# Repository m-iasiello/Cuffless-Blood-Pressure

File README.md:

# Cuffless-Blood-Pressure
Cuffless Blood Pressure monitor using custom PCB developed from AD8232 HRM and Si1143 pulse ox.  Includes several .ino, pcb schems, and solidworks builds.

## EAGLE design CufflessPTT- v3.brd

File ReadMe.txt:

This folder contains the relevant schematic and files for the Spring 2018 Cuffless Blood Pressure Measurement Project

Contents:

	Powerpoints
		- Tutorial Presentation: Background information and initial project proposal
		- Update Presentations: Updates on progress through the semester
		- Final Presentation: Overall presentation of the project, work, and results

	Schematic and PCB Layout
		- CufflessPTT-v3.sch: The Eagle schematic for the PTT Measurement PCB 
		- CufflessPTT-v3.brd: The Eagle layout for the PTT Measurement PCB

	Software
		- PTT-BP.ino: The main Arduino code file for BP measurement.  
		- QRS_detection.ino: QRS detection algorithm for R wave detection
		- Si1143_pulse_demo.ino: Driver software for the Si1143, as well as helper functions for identification of the PPG signals
		- CUFFLESS.apk: Installer file for the Cuffless Android app.

	Solidworks Files
		- CAD files for the Cuffless case, as well as the locking pin to hold the case together.

Instructions for use:
	
	1. Install the Android app on an Android phone. 
	2. Press the button on the side to turn on the device. The LEDs should come on.
	3. Pair the Android app with the device by opening the app, and then find and pair to the device named HC-06.
	4. Press the start measurement button.
	5. Hold the electrode side of the device against the inside of your wrist. 
	6. Hold one finger of your opposite firmly on the electrdoe on top, and another finger firmly across the LEDs and photodiode.
	7. The device should display measurements as they are acquired.

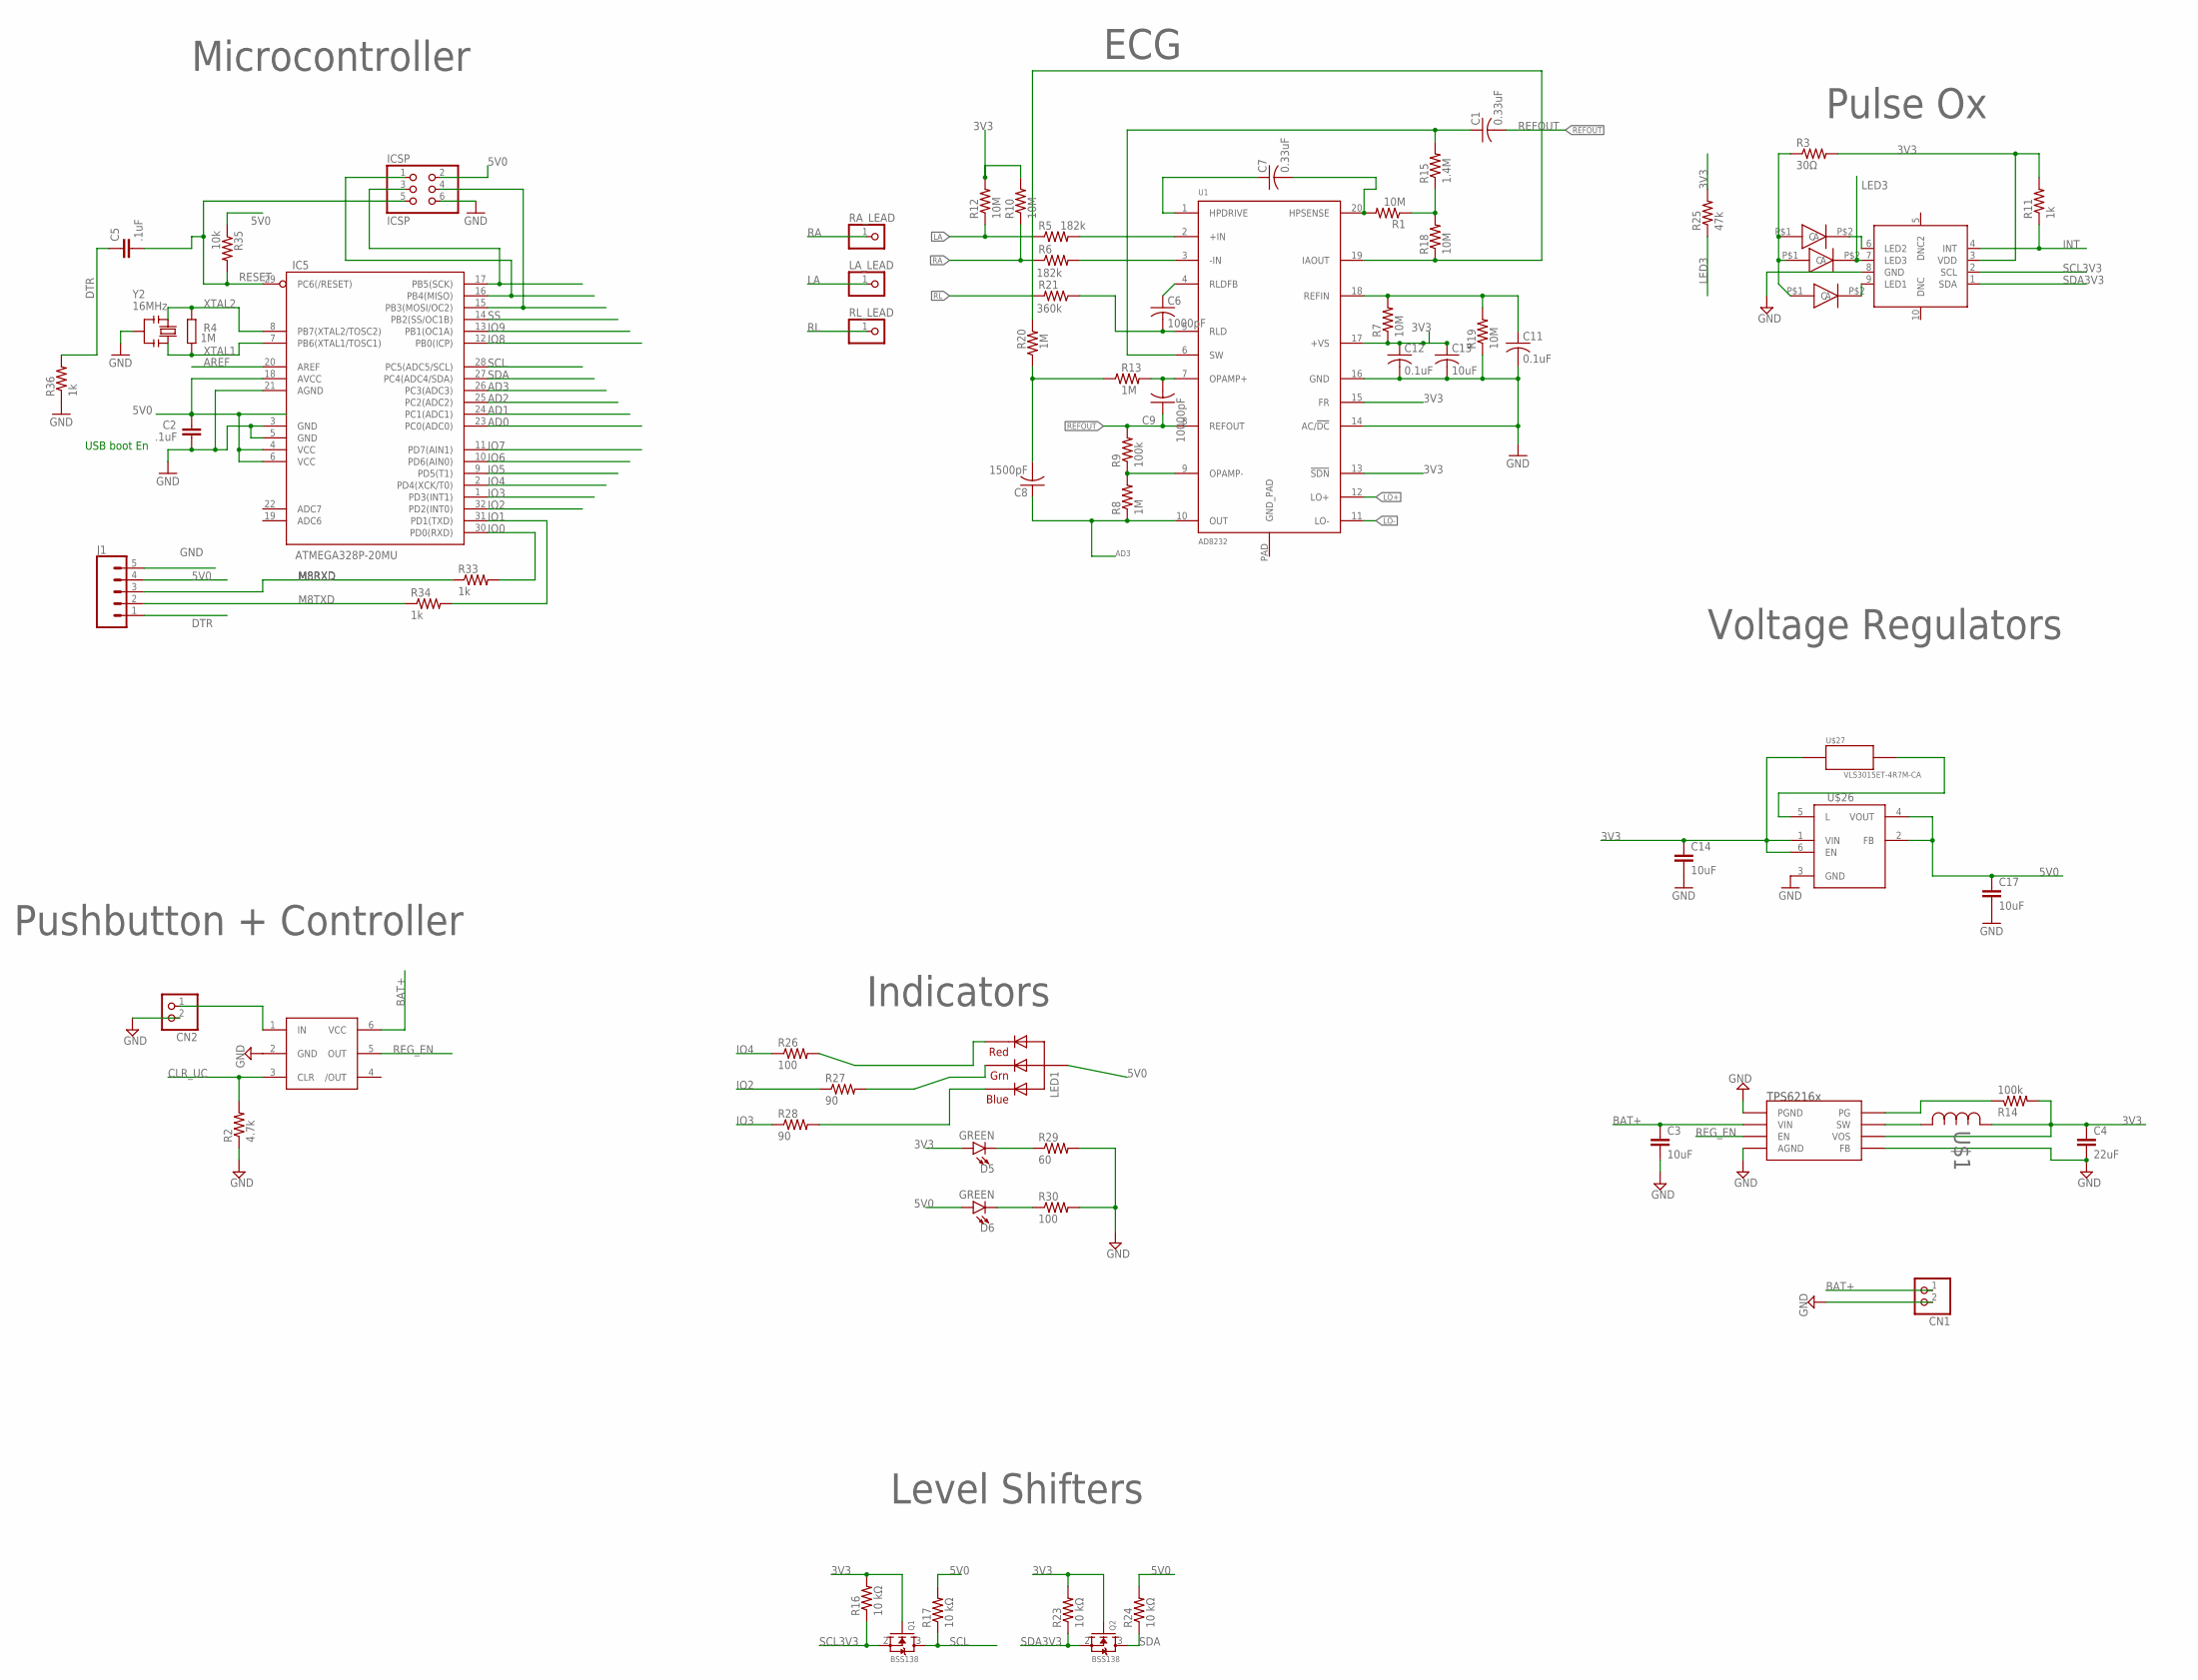
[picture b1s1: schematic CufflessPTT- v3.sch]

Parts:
C1, C7: 0.33uF; C0603
C2, C5: .1uF; C0603-ROUND
C3, C14, C17: 10uF; C0603; MPN MCNP16V105M5X11
C4: 22uF; C0805
C6: 1000pF; C0603
C8: 1500pF; C0603
C9: 10000pF; C0603
C11, C12: 0.1uF; C0603
C13: 10uF; C0603
CN1, CN2: JST_2PIN-THM; JST-PH-2-THM
D5, D6: GREEN; LED-0603
IC5: ATMEGA328P-20MU; MLF32
ICSP: ICSP; 2X03
J1: CONN_05; 1X05
LA_LEAD: PINHD-1X1; 1X01
LED1: RGBLED_CA-5MM; LED5MMRGB
LED2, LED3, LED4: SMD_COMBO
Q1, Q2: BSS138; SOT23-3
R1, R7, R10, R12, R18, R19: 10M; 0603-RES
R2: 4.7k; R0402
R3: 30Ω; R0402
R4: 1M; R0603-ROUND
R5, R6: 182k; 0603-RES
R8, R13, R20: 1M; 0603-RES
R9: 100k; 0603-RES
R11, R33, R34, R36: 1k; R0402
R14: 100k; R0402
R15: 1.4M; 0603-RES
R16, R17, R23, R24: 10 kΩ; R0402
R21: 360k; 0603-RES
R25: 47k; R0402
R26, R30: 100; R0402
R27, R28: 90; R0402
R29: 60; R0402
R35: 10k; R0402
RA_LEAD: PINHD-1X1; 1X01
RL_LEAD: PINHD-1X1; 1X01
U1: AD8232; LFCSP_20
U$1: VLF3012ST-2R2M1R4; IND_3010
U$4: SI1143; QFN-10
U$5: TPS6216X; 8WSON
U$15: MAX16054; TSOT23-6
U$26: TPS61222; SOT363_6SOIC
U$27: VLS3015ET-4R7M-CA
Y2: 16MHz; RESONATOR

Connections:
3V3: C4.1, C12.1, C13.1, C14.1, D5.A, Q1.1 (G), Q2.1 (G), R3.2, R7.1, R10.2, R11.2, R12.2, R14.2, R16.2, R23.2, R25.2, U1.13 (!SDN), U1.15 (FR), U1.17 (+VS), U$1.1, U$4.3 (VDD), U$5.P$6 (VOS), U$26.1 (VIN), U$26.6 (EN), U$27.1
5V0: C2.2, C17.1, D6.A, IC5.4 (VCC), IC5.6 (VCC), IC5.18 (AVCC), ICSP.2, J1.4, LED1.2 (VCC), R17.2, R24.2, R35.1, U$26.2 (FB), U$26.4 (VOUT)
AD0: IC5.23 (PC0(ADC0))
AD1: IC5.24 (PC1(ADC1))
AD2: IC5.25 (PC2(ADC2))
AD3: C8.1, IC5.26 (PC3(ADC3)), R8.1, U1.10 (OUT)
AREF: IC5.20 (AREF)
BAT+: C3.1, CN1.1 (2), U$5.P$2 (VIN), U$15.6 (VCC)
CLR_UC: R2.2, U$15.3 (CLR)
DTR: C5.1, J1.1, R36.2
GND: C2.1, C3.2, C4.2, C11.2, C12.2, C13.2, C14.2, C17.2, CN1.2 (1), CN2.2 (1), IC5.3 (GND), IC5.5 (GND), IC5.21 (AGND), ICSP.6, J1.5, R2.1, R19.1, R29.2, R30.2, R36.1, U1.14 (AC/!DC), U1.16 (GND), U$4.8 (GND), U$5.P$1 (PGND), U$5.P$4 (AGND), U$5.P$5 (FB), U$5.P$9 (AGND), U$15.2 (GND), U$26.3 (GND), Y2.2
INT: R11.1, U$4.4 (INT)
IO0: IC5.30 (PD0(RXD)), R33.2
IO1: IC5.31 (PD1(TXD)), R34.2
IO2: IC5.32 (PD2(INT0)), R27.1
IO3: IC5.1 (PD3(INT1)), R28.1
IO4: IC5.2 (PD4(XCK/T0)), R26.1
IO5: IC5.9 (PD5(T1))
IO6: IC5.10 (PD6(AIN0))
IO7: IC5.11 (PD7(AIN1))
IO8: IC5.12 (PB0(ICP))
IO9: IC5.13 (PB1(OC1A))
LA: LA_LEAD.1, R5.1, R12.1
LED3: LED2.P$2 (C), R25.1, U$4.7 (LED3)
LO+: U1.12 (LO+)
LO-: U1.11 (LO-)
M8RXD: J1.3, R33.1
M8TXD: J1.2, R34.1
MISO: IC5.16 (PB4(MISO)), ICSP.1
MOSI: IC5.15 (PB3(MOSI/OC2)), ICSP.4
unnamed: R5.2, U1.2 (+IN)
unnamed: CN2.1 (2), U$15.1 (IN)
unnamed: C1.1, R15.2, U1.6 (SW)
unnamed: R1.1, R15.1, R18.2
unnamed: C8.2, R13.1, R20.1
unnamed: R14.1, U$5.P$8 (PG)
unnamed: R6.2, U1.3 (-IN)
unnamed: C9.2, R13.2, U1.7 (OPAMP+)
unnamed: D5.C, R29.1
unnamed: C7.2, R1.2, U1.20 (HPSENSE)
unnamed: C11.1, R7.2, R19.2, U1.18 (REFIN)
unnamed: U$1.2, U$5.P$7 (SW)
unnamed: R8.2, R9.1, U1.9 (OPAMP-)
unnamed: C7.1, U1.1 (HPDRIVE)
unnamed: C6.1, U1.4 (RLDFB)
unnamed: D6.C, R30.1
unnamed: R18.1, R20.2, U1.19 (IAOUT)
unnamed: C6.2, R21.1, U1.5 (RLD)
unnamed: LED2.P$1 (A), LED3.P$1 (A), LED4.P$1 (A), R3.1
unnamed: U$26.5 (L), U$27.2
unnamed: LED3.P$2 (C), U$4.6 (LED2)
unnamed: LED1.4 (BLUE), R28.2
unnamed: LED1.3 (GREEN), R27.2
unnamed: LED1.1 (RED), R26.2
unnamed: LED4.P$2 (C), U$4.9 (LED1)
RA: R6.1, R10.1, RA_LEAD.1
REFOUT: C1.2, C9.1, R9.2, U1.8 (REFOUT)
REG_EN: U$5.P$3 (EN), U$15.5 (OUT)
RESET: C5.2, IC5.29 (PC6(/RESET)), ICSP.5, R35.2
RL: R21.2, RL_LEAD.1
SCK: IC5.17 (PB5(SCK)), ICSP.3
SCL: IC5.28 (PC5(ADC5/SCL)), Q1.3 (D), R17.1
SCL3V3: Q1.2 (S), R16.1, U$4.2 (SCL)
SDA: IC5.27 (PC4(ADC4/SDA)), Q2.3 (D), R24.1
SDA3V3: Q2.2 (S), R23.1, U$4.1 (SDA)
SS: IC5.14 (PB2(SS/OC1B))
XTAL1: IC5.7 (PB6(XTAL1/TOSC1)), R4.1, Y2.3
XTAL2: IC5.8 (PB7(XTAL2/TOSC2)), R4.2, Y2.1

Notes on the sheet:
Voltage Regulators
Pulse Ox
Pushbutton + Controller
ECG
USB boot En
Indicators
Microcontroller
Level Shifters

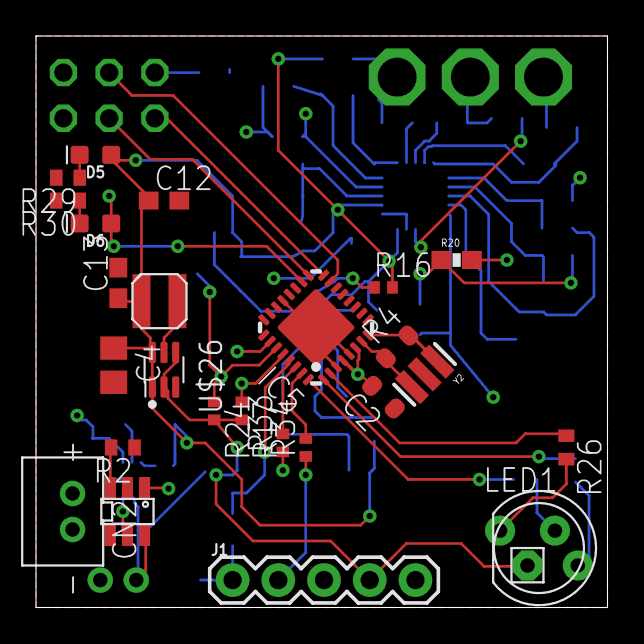
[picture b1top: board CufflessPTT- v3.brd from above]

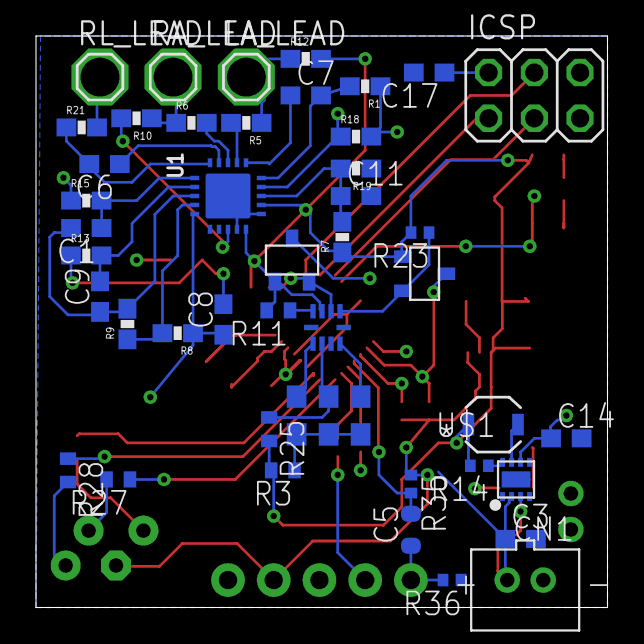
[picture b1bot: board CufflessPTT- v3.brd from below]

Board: 4 copper layers, 31.8 x 31.8 mm, 71 parts (46 on the bottom side), 56 nets.

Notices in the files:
parts and their libraries:
SparkFun-Passives: Licensing: CC v3.0 Share-Alike You are welcome to use this library for commercial purposes.
SparkFun-LED: Licensing: Creative Commons ShareAlike 4.0 International - https://creativecommons.org/licenses/by-sa/4.0
